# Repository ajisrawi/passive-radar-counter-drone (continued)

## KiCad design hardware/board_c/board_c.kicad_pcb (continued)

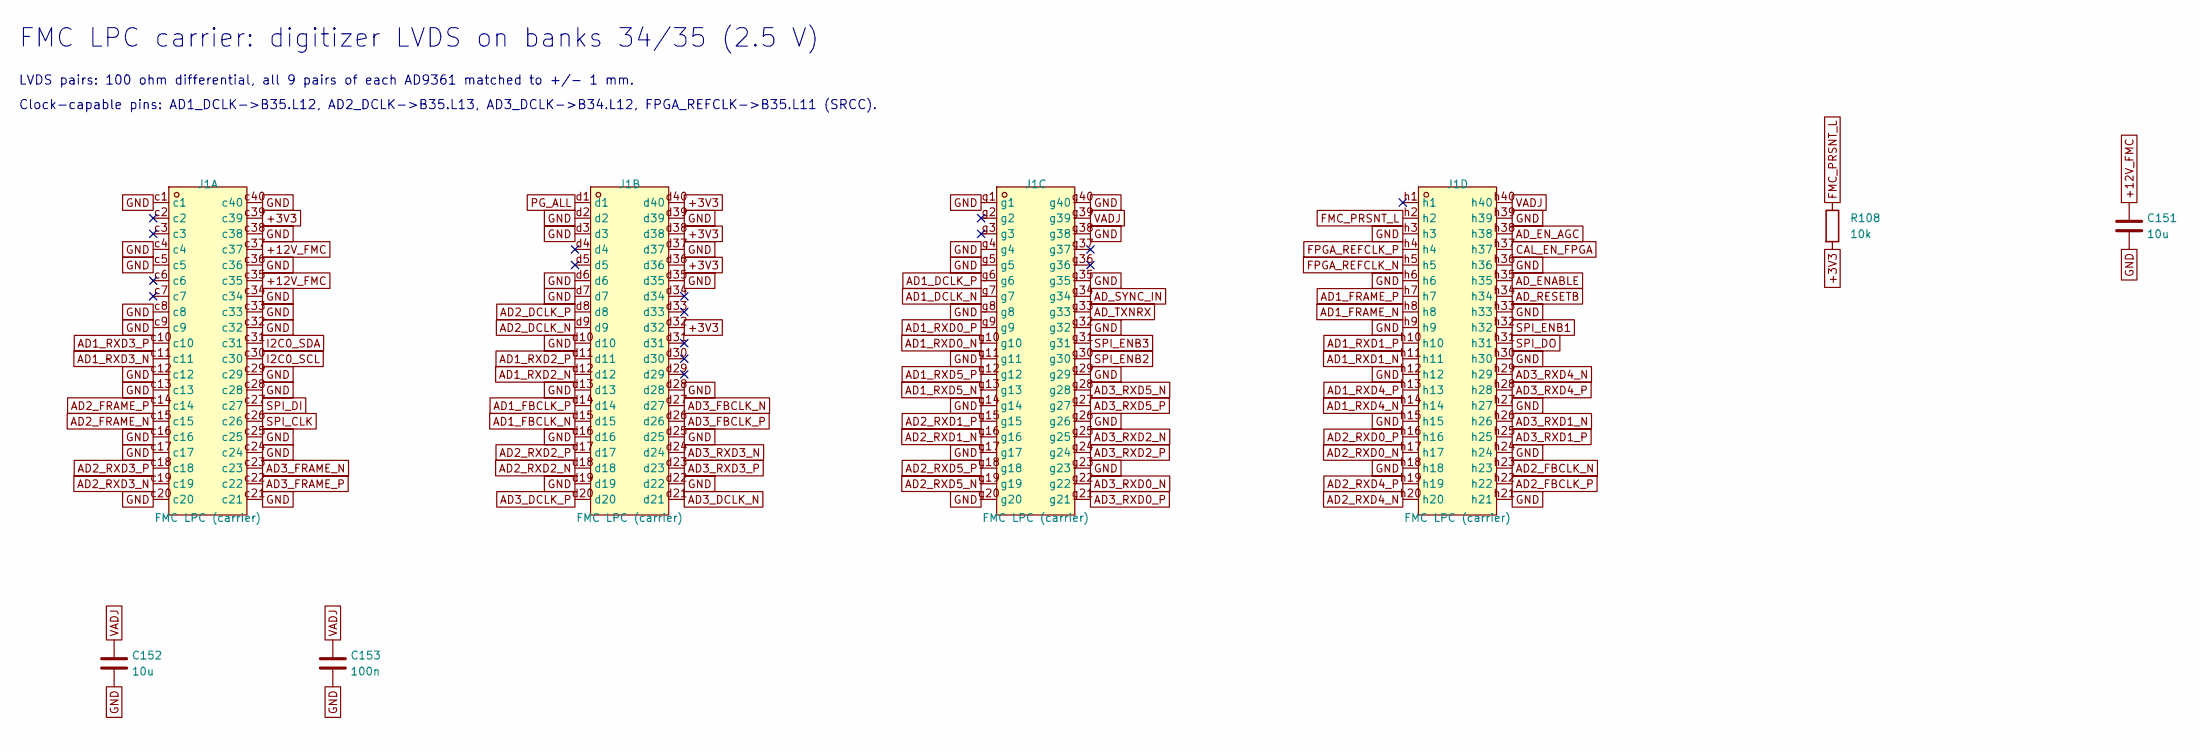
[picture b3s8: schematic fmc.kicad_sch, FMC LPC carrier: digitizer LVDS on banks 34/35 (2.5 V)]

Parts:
C151: 10u; C_0805_2012Metric
C152: 10u; C_0603_1608Metric; LCSC C19702
C153: 100n; C_0402_1005Metric; LCSC C1525
J1: FMC LPC (carrier); BGA-160_L56.6-W13.2-R4-C40-P1.27-BR; MPN ASP-134603-01; LCSC C2836665
R108: 10k; R_0402_1005Metric; LCSC C25744

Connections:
+3V3: J1.c39, J1.d32, J1.d36, J1.d38, J1.d40, R108.2; also elsewhere on the board
+12V_FMC: C151.1, J1.c35, J1.c37; also elsewhere on the board
AD1_DCLK_N: J1.g7; also elsewhere on the board
AD1_DCLK_P: J1.g6; also elsewhere on the board
AD1_FBCLK_N: J1.d15; also elsewhere on the board
AD1_FBCLK_P: J1.d14; also elsewhere on the board
AD1_FRAME_N: J1.h8; also elsewhere on the board
AD1_FRAME_P: J1.h7; also elsewhere on the board
AD1_RXD0_N: J1.g10; also elsewhere on the board
AD1_RXD0_P: J1.g9; also elsewhere on the board
AD1_RXD1_N: J1.h11; also elsewhere on the board
AD1_RXD1_P: J1.h10; also elsewhere on the board
AD1_RXD2_N: J1.d12; also elsewhere on the board
AD1_RXD2_P: J1.d11; also elsewhere on the board
AD1_RXD3_N: J1.c11; also elsewhere on the board
AD1_RXD3_P: J1.c10; also elsewhere on the board
AD1_RXD4_N: J1.h14; also elsewhere on the board
AD1_RXD4_P: J1.h13; also elsewhere on the board
AD1_RXD5_N: J1.g13; also elsewhere on the board
AD1_RXD5_P: J1.g12; also elsewhere on the board
AD2_DCLK_N: J1.d9; also elsewhere on the board
AD2_DCLK_P: J1.d8; also elsewhere on the board
AD2_FBCLK_N: J1.h23; also elsewhere on the board
AD2_FBCLK_P: J1.h22; also elsewhere on the board
AD2_FRAME_N: J1.c15; also elsewhere on the board
AD2_FRAME_P: J1.c14; also elsewhere on the board
AD2_RXD0_N: J1.h17; also elsewhere on the board
AD2_RXD0_P: J1.h16; also elsewhere on the board
AD2_RXD1_N: J1.g16; also elsewhere on the board
AD2_RXD1_P: J1.g15; also elsewhere on the board
AD2_RXD2_N: J1.d18; also elsewhere on the board
AD2_RXD2_P: J1.d17; also elsewhere on the board
AD2_RXD3_N: J1.c19; also elsewhere on the board
AD2_RXD3_P: J1.c18; also elsewhere on the board
AD2_RXD4_N: J1.h20; also elsewhere on the board
AD2_RXD4_P: J1.h19; also elsewhere on the board
AD2_RXD5_N: J1.g19; also elsewhere on the board
AD2_RXD5_P: J1.g18; also elsewhere on the board
AD3_DCLK_N: J1.d21; also elsewhere on the board
AD3_DCLK_P: J1.d20; also elsewhere on the board
AD3_FBCLK_N: J1.d27; also elsewhere on the board
AD3_FBCLK_P: J1.d26; also elsewhere on the board
AD3_FRAME_N: J1.c23; also elsewhere on the board
AD3_FRAME_P: J1.c22; also elsewhere on the board
AD3_RXD0_N: J1.g22; also elsewhere on the board
AD3_RXD0_P: J1.g21; also elsewhere on the board
AD3_RXD1_N: J1.h26; also elsewhere on the board
AD3_RXD1_P: J1.h25; also elsewhere on the board
AD3_RXD2_N: J1.g25; also elsewhere on the board
AD3_RXD2_P: J1.g24; also elsewhere on the board
AD3_RXD3_N: J1.d24; also elsewhere on the board
AD3_RXD3_P: J1.d23; also elsewhere on the board
AD3_RXD4_N: J1.h29; also elsewhere on the board
AD3_RXD4_P: J1.h28; also elsewhere on the board
AD3_RXD5_N: J1.g28; also elsewhere on the board
AD3_RXD5_P: J1.g27; also elsewhere on the board
AD_ENABLE: J1.h35; also elsewhere on the board
AD_EN_AGC: J1.h38; also elsewhere on the board
AD_RESETB: J1.h34; also elsewhere on the board
AD_SYNC_IN: J1.g34; also elsewhere on the board
AD_TXNRX: J1.g33; also elsewhere on the board
CAL_EN_FPGA: J1.h37; also elsewhere on the board
FMC_PRSNT_L: J1.h2, R108.1; also elsewhere on the board
FPGA_REFCLK_N: J1.h5; also elsewhere on the board
FPGA_REFCLK_P: J1.h4; also elsewhere on the board
GND: C151.2, C152.2, C153.2, J1.c1, J1.c4, J1.c5, J1.c8, J1.c9, J1.c12, J1.c13, J1.c16, J1.c17, J1.c20, J1.c21, J1.c24, J1.c25, J1.c28, J1.c29, J1.c32, J1.c33, J1.c34, J1.c36, J1.c38, J1.c40, J1.d2, J1.d3, J1.d6, J1.d7, J1.d10, J1.d13, J1.d16, J1.d19, J1.d22, J1.d25, J1.d28, J1.d35, J1.d37, J1.d39, J1.g1, J1.g4, J1.g5, J1.g8, J1.g11, J1.g14, J1.g17, J1.g20, J1.g23, J1.g26, J1.g29, J1.g32, J1.g35, J1.g38, J1.g40, J1.h3, J1.h6, J1.h9, J1.h12, J1.h15, J1.h18, J1.h21, J1.h24, J1.h27, J1.h30, J1.h33, J1.h36, J1.h39; also elsewhere on the board
I2C0_SCL: J1.c30; also elsewhere on the board
I2C0_SDA: J1.c31; also elsewhere on the board
PG_ALL: J1.d1; also elsewhere on the board
SPI_CLK: J1.c26; also elsewhere on the board
SPI_DI: J1.c27; also elsewhere on the board
SPI_DO: J1.h31; also elsewhere on the board
SPI_ENB1: J1.h32; also elsewhere on the board
SPI_ENB2: J1.g30; also elsewhere on the board
SPI_ENB3: J1.g31; also elsewhere on the board
VADJ: C152.1, C153.1, J1.g39, J1.h40; also elsewhere on the board

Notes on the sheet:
FMC LPC carrier: digitizer LVDS on banks 34/35 (2.5 V)
LVDS pairs: 100 ohm differential, all 9 pairs of each AD9361 matched to +/- 1 mm.
Clock-capable pins: AD1_DCLK->B35.L12, AD2_DCLK->B35.L13, AD3_DCLK->B34.L12, FPGA_REFCLK->B35.L11 (SRCC).

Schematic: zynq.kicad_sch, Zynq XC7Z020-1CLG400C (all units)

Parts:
U1: XC7Z020-1CLG400C; FBGA-400_L17.0-W17.0-R20-C20-P0.80-TL; MPN XC7Z020-1CLG400C; LCSC C2988113

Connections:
+1V0: U1.G7 (VCCPINT), U1.G11 (VCCBRAM), U1.G13 (VCCINT), U1.H10 (VCCBRAM), U1.H12 (VCCINT), U1.J7 (VCCPINT), U1.J13 (VCCINT), U1.K12 (VCCINT), U1.L7 (VCCPINT), U1.L13 (VCCINT), U1.M12 (VCCINT), U1.N7 (VCCPINT), U1.N13 (VCCINT), U1.P8 (VCCPINT), U1.P12 (VCCINT), U1.R7 (VCCPINT), U1.R13 (VCCINT); also elsewhere on the board
+1V8: U1.F8 (VCCPAUX), U1.G9 (VCCPAUX), U1.H8 (VCCPAUX), U1.J11 (VCCAUX), U1.K8 (VCCPAUX), U1.L11 (VCCAUX), U1.M8 (VCCPAUX), U1.N9 (VCCAUX), U1.N11 (VCCAUX), U1.P10 (VCCAUX), U1.R9 (VCCAUX); also elsewhere on the board
+1V35: U1.A3 (VCCO_DDR_502), U1.D2 (VCCO_DDR_502), U1.E5 (VCCO_DDR_502), U1.G1 (VCCO_DDR_502), U1.H4 (VCCO_DDR_502), U1.L3 (VCCO_DDR_502), U1.P2 (VCCO_DDR_502), U1.R5 (VCCO_DDR_502), U1.U1 (VCCO_DDR_502), U1.V4 (VCCO_DDR_502); also elsewhere on the board
+3V3: U1.A13 (VCCO_MIO1_501), U1.B6 (VCCO_MIO0_500), U1.B16 (VCCO_MIO1_501), U1.D7 (VCCO_MIO0_500), U1.D12 (VCCO_MIO1_501), U1.E15 (VCCO_MIO1_501), U1.K6 (VCCO_0), U1.M6 (CFGBVS_0), U1.N6 (RSVDVCC3), U1.R6 (RSVDVCC2), U1.T6 (RSVDVCC1), U1.T8 (VCCO_13), U1.U11 (VCCO_13), U1.W7 (VCCO_13), U1.Y10 (VCCO_13); also elsewhere on the board
AD1_DCLK_N: U1.K18 (IO_L12N_T1_MRCC_35); also elsewhere on the board
AD1_DCLK_P: U1.K17 (IO_L12P_T1_MRCC_35); also elsewhere on the board
AD1_FBCLK_N: U1.M18 (IO_L8N_T1_AD10N_35); also elsewhere on the board
AD1_FBCLK_P: U1.M17 (IO_L8P_T1_AD10P_35); also elsewhere on the board
AD1_FRAME_N: U1.B20 (IO_L1N_T0_AD0N_35); also elsewhere on the board
AD1_FRAME_P: U1.C20 (IO_L1P_T0_AD0P_35); also elsewhere on the board
AD1_RXD0_N: U1.A20 (IO_L2N_T0_AD8N_35); also elsewhere on the board
AD1_RXD0_P: U1.B19 (IO_L2P_T0_AD8P_35); also elsewhere on the board
AD1_RXD1_N: U1.D18 (IO_L3N_T0_DQS_AD1N_35); also elsewhere on the board
AD1_RXD1_P: U1.E17 (IO_L3P_T0_DQS_AD1P_35); also elsewhere on the board
AD1_RXD2_N: U1.D20 (IO_L4N_T0_35); also elsewhere on the board
AD1_RXD2_P: U1.D19 (IO_L4P_T0_35); also elsewhere on the board
AD1_RXD3_N: U1.E19 (IO_L5N_T0_AD9N_35); also elsewhere on the board
AD1_RXD3_P: U1.E18 (IO_L5P_T0_AD9P_35); also elsewhere on the board
AD1_RXD4_N: U1.F17 (IO_L6N_T0_VREF_35); also elsewhere on the board
AD1_RXD4_P: U1.F16 (IO_L6P_T0_35); also elsewhere on the board
AD1_RXD5_N: U1.M20 (IO_L7N_T1_AD2N_35); also elsewhere on the board
AD1_RXD5_P: U1.M19 (IO_L7P_T1_AD2P_35); also elsewhere on the board
AD2_DCLK_N: U1.H17 (IO_L13N_T2_MRCC_35); also elsewhere on the board
AD2_DCLK_P: U1.H16 (IO_L13P_T2_MRCC_35); also elsewhere on the board
AD2_FBCLK_N: U1.G15 (IO_L19N_T3_VREF_35); also elsewhere on the board
AD2_FBCLK_P: U1.H15 (IO_L19P_T3_35); also elsewhere on the board
AD2_FRAME_N: U1.L20 (IO_L9N_T1_DQS_AD3N_35); also elsewhere on the board
AD2_FRAME_P: U1.L19 (IO_L9P_T1_DQS_AD3P_35); also elsewhere on the board
AD2_RXD0_N: U1.J19 (IO_L10N_T1_AD11N_35); also elsewhere on the board
AD2_RXD0_P: U1.K19 (IO_L10P_T1_AD11P_35); also elsewhere on the board
AD2_RXD1_N: U1.H18 (IO_L14N_T2_AD4N_SRCC_35); also elsewhere on the board
AD2_RXD1_P: U1.J18 (IO_L14P_T2_AD4P_SRCC_35); also elsewhere on the board
AD2_RXD2_N: U1.F20 (IO_L15N_T2_DQS_AD12N_35); also elsewhere on the board
AD2_RXD2_P: U1.F19 (IO_L15P_T2_DQS_AD12P_35); also elsewhere on the board
AD2_RXD3_N: U1.G18 (IO_L16N_T2_35); also elsewhere on the board
AD2_RXD3_P: U1.G17 (IO_L16P_T2_35); also elsewhere on the board
AD2_RXD4_N: U1.H20 (IO_L17N_T2_AD5N_35); also elsewhere on the board
AD2_RXD4_P: U1.J20 (IO_L17P_T2_AD5P_35); also elsewhere on the board
AD2_RXD5_N: U1.G20 (IO_L18N_T2_AD13N_35); also elsewhere on the board
AD2_RXD5_P: U1.G19 (IO_L18P_T2_AD13P_35); also elsewhere on the board
AD3_DCLK_N: U1.U19 (IO_L12N_T1_MRCC_34); also elsewhere on the board
AD3_DCLK_P: U1.U18 (IO_L12P_T1_MRCC_34); also elsewhere on the board
AD3_FBCLK_N: U1.U17 (IO_L9N_T1_DQS_34); also elsewhere on the board
AD3_FBCLK_P: U1.T16 (IO_L9P_T1_DQS_34); also elsewhere on the board
AD3_FRAME_N: U1.T10 (IO_L1N_T0_34); also elsewhere on the board
AD3_FRAME_P: U1.T11 (IO_L1P_T0_34); also elsewhere on the board
AD3_RXD0_N: U1.U12 (IO_L2N_T0_34); also elsewhere on the board
AD3_RXD0_P: U1.T12 (IO_L2P_T0_34); also elsewhere on the board
AD3_RXD1_N: U1.W13 (IO_L4N_T0_34); also elsewhere on the board
AD3_RXD1_P: U1.V12 (IO_L4P_T0_34); also elsewhere on the board
AD3_RXD2_N: U1.T15 (IO_L5N_T0_34); also elsewhere on the board
AD3_RXD2_P: U1.T14 (IO_L5P_T0_34); also elsewhere on the board
AD3_RXD3_N: U1.R14 (IO_L6N_T0_VREF_34); also elsewhere on the board
AD3_RXD3_P: U1.P14 (IO_L6P_T0_34); also elsewhere on the board
AD3_RXD4_N: U1.Y17 (IO_L7N_T1_34); also elsewhere on the board
AD3_RXD4_P: U1.Y16 (IO_L7P_T1_34); also elsewhere on the board
AD3_RXD5_N: U1.Y14 (IO_L8N_T1_34); also elsewhere on the board
AD3_RXD5_P: U1.W14 (IO_L8P_T1_34); also elsewhere on the board
AD_ENABLE: U1.P20 (IO_L14N_T2_SRCC_34); also elsewhere on the board
AD_EN_AGC: U1.W20 (IO_L16N_T2_34); also elsewhere on the board
AD_RESETB: U1.N20 (IO_L14P_T2_SRCC_34); also elsewhere on the board
AD_SYNC_IN: U1.U20 (IO_L15N_T2_DQS_34); also elsewhere on the board
AD_TXNRX: U1.T20 (IO_L15P_T2_DQS_34); also elsewhere on the board
CAL_EN_FPGA: U1.V20 (IO_L16P_T2_34); also elsewhere on the board
DDR_A0: U1.N2 (PS_DDR_A0_502); also elsewhere on the board
DDR_A1: U1.K2 (PS_DDR_A1_502); also elsewhere on the board
DDR_A2: U1.M3 (PS_DDR_A2_502); also elsewhere on the board
DDR_A3: U1.K3 (PS_DDR_A3_502); also elsewhere on the board
DDR_A4: U1.M4 (PS_DDR_A4_502); also elsewhere on the board
DDR_A5: U1.L1 (PS_DDR_A5_502); also elsewhere on the board
DDR_A6: U1.L4 (PS_DDR_A6_502); also elsewhere on the board
DDR_A7: U1.K4 (PS_DDR_A7_502); also elsewhere on the board
DDR_A8: U1.K1 (PS_DDR_A8_502); also elsewhere on the board
DDR_A9: U1.J4 (PS_DDR_A9_502); also elsewhere on the board
DDR_A10: U1.F5 (PS_DDR_A10_502); also elsewhere on the board
DDR_A11: U1.G4 (PS_DDR_A11_502); also elsewhere on the board
DDR_A12: U1.E4 (PS_DDR_A12_502); also elsewhere on the board
DDR_A13: U1.D4 (PS_DDR_A13_502); also elsewhere on the board
DDR_A14: U1.F4 (PS_DDR_A14_502); also elsewhere on the board
DDR_BA0: U1.L5 (PS_DDR_BA0_502); also elsewhere on the board
DDR_BA1: U1.R4 (PS_DDR_BA1_502); also elsewhere on the board
DDR_BA2: U1.J5 (PS_DDR_BA2_502); also elsewhere on the board
DDR_CAS_B: U1.P5 (PS_DDR_CAS_B_502); also elsewhere on the board
DDR_CKE: U1.N3 (PS_DDR_CKE_502); also elsewhere on the board
DDR_CK_N: U1.M2 (PS_DDR_CKN_502); also elsewhere on the board
DDR_CK_P: U1.L2 (PS_DDR_CKP_502); also elsewhere on the board
DDR_CS_B: U1.N1 (PS_DDR_CS_B_502); also elsewhere on the board
DDR_DM0: U1.A1 (PS_DDR_DM0_502); also elsewhere on the board
DDR_DM1: U1.F1 (PS_DDR_DM1_502); also elsewhere on the board
DDR_DQ0: U1.C3 (PS_DDR_DQ0_502); also elsewhere on the board
DDR_DQ1: U1.B3 (PS_DDR_DQ1_502); also elsewhere on the board
DDR_DQ2: U1.A2 (PS_DDR_DQ2_502); also elsewhere on the board
DDR_DQ3: U1.A4 (PS_DDR_DQ3_502); also elsewhere on the board
DDR_DQ4: U1.D3 (PS_DDR_DQ4_502); also elsewhere on the board
DDR_DQ5: U1.D1 (PS_DDR_DQ5_502); also elsewhere on the board
DDR_DQ6: U1.C1 (PS_DDR_DQ6_502); also elsewhere on the board
DDR_DQ7: U1.E1 (PS_DDR_DQ7_502); also elsewhere on the board
DDR_DQ8: U1.E2 (PS_DDR_DQ8_502); also elsewhere on the board
DDR_DQ9: U1.E3 (PS_DDR_DQ9_502); also elsewhere on the board
DDR_DQ10: U1.G3 (PS_DDR_DQ10_502); also elsewhere on the board
DDR_DQ11: U1.H3 (PS_DDR_DQ11_502); also elsewhere on the board
DDR_DQ12: U1.J3 (PS_DDR_DQ12_502); also elsewhere on the board
DDR_DQ13: U1.H2 (PS_DDR_DQ13_502); also elsewhere on the board
DDR_DQ14: U1.H1 (PS_DDR_DQ14_502); also elsewhere on the board
DDR_DQ15: U1.J1 (PS_DDR_DQ15_502); also elsewhere on the board
DDR_DQS0_N: U1.B2 (PS_DDR_DQS_N0_502); also elsewhere on the board
DDR_DQS0_P: U1.C2 (PS_DDR_DQS_P0_502); also elsewhere on the board
DDR_DQS1_N: U1.F2 (PS_DDR_DQS_N1_502); also elsewhere on the board
DDR_DQS1_P: U1.G2 (PS_DDR_DQS_P1_502); also elsewhere on the board
DDR_ODT: U1.N5 (PS_DDR_ODT_502); also elsewhere on the board
DDR_RAS_B: U1.P4 (PS_DDR_RAS_B_502); also elsewhere on the board
DDR_RESET_B: U1.B4 (PS_DDR_DRST_B_502); also elsewhere on the board
DDR_VREF: U1.H6 (PS_DDR_VREF0_502), U1.P6 (PS_DDR_VREF1_502); also elsewhere on the board
DDR_VRN: U1.G5 (PS_DDR_VRN_502); also elsewhere on the board
DDR_VRP: U1.H5 (PS_DDR_VRP_502); also elsewhere on the board
DDR_WE_B: U1.M5 (PS_DDR_WE_B_502); also elsewhere on the board
DONE: U1.R11 (DONE_0); also elsewhere on the board
ETH_MDC: U1.C10 (PS_MIO52_501); also elsewhere on the board
ETH_MDIO: U1.C11 (PS_MIO53_501); also elsewhere on the board
ETH_RSTN: U1.B14 (PS_MIO47_501); also elsewhere on the board
FMC_PRSNT_L: U1.Y9 (IO_L14P_T2_SRCC_13); also elsewhere on the board
FPGA_REFCLK_N: U1.L17 (IO_L11N_T1_SRCC_35); also elsewhere on the board
FPGA_REFCLK_P: U1.L16 (IO_L11P_T1_SRCC_35); also elsewhere on the board
GND: U1.A8 (GND), U1.A18 (GND), U1.B1 (GND), U1.B11 (GND), U1.C4 (GND), U1.C9 (GND), U1.C14 (GND), U1.D17 (GND), U1.E10 (GND), U1.E20 (GND), U1.F3 (GND), U1.F7 (GND), U1.F10 (RSVDGND), U1.F11 (VCCBATT_0), U1.G10 (GND), U1.G12 (GND), U1.G16 (GND), U1.H7 (GND), U1.H9 (GND), U1.H11 (GND), U1.H13 (GND), U1.H19 (GND), U1.J2 (GND), U1.J8 (GND), U1.J12 (GND), U1.K5 (GND), U1.K7 (GND), U1.K11 (GND), U1.K13 (GND), U1.K15 (GND), U1.L8 (GND), U1.L12 (GND), U1.L18 (GND), U1.M1 (GND), U1.M7 (GND), U1.M11 (GND), U1.M13 (GND), U1.N4 (GND), U1.N8 (GND), U1.N10 (GND), U1.N12 (GND), U1.N14 (GND), U1.P7 (GND), U1.P9 (GND), U1.P11 (GND), U1.P13 (GND), U1.P17 (GND), U1.R8 (GND), U1.R12 (GND), U1.R20 (GND), U1.T3 (GND), U1.T7 (GND), U1.T13 (GND), U1.U6 (GND), U1.U16 (GND), U1.V9 (GND), U1.V19 (GND), U1.W2 (GND), U1.W12 (GND), U1.Y5 (GND), U1.Y15 (GND); also elsewhere on the board
GNDADC: U1.J10 (GNDADC_0), U1.K9 (VP_0), U1.K10 (VREFN_0), U1.L9 (VREFP_0), U1.L10 (VN_0); also elsewhere on the board
GNSS_PPS: U1.U7 (IO_L11P_T1_SRCC_13); also elsewhere on the board
GNSS_RESETN: U1.U10 (IO_L12N_T1_MRCC_13); also elsewhere on the board
GNSS_RXD: U1.T9 (IO_L12P_T1_MRCC_13); also elsewhere on the board
GNSS_TXD: U1.V7 (IO_L11N_T1_SRCC_13); also elsewhere on the board
I2C0_SCL: U1.E9 (PS_MIO10_500); also elsewhere on the board
I2C0_SDA: U1.C6 (PS_MIO11_500); also elsewhere on the board
INIT_B: U1.R10 (INIT_B_0); also elsewhere on the board
JTAG_TCK: U1.F9 (TCK_0); also elsewhere on the board
JTAG_TDI: U1.G6 (TDI_0); also elsewhere on the board
JTAG_TDO: U1.F6 (TDO_0); also elsewhere on the board
JTAG_TMS: U1.J6 (TMS_0); also elsewhere on the board
LED_PL0: U1.Y7 (IO_L13P_T2_MRCC_13); also elsewhere on the board
LED_PL1: U1.Y6 (IO_L13N_T2_MRCC_13); also elsewhere on the board
LED_PS: U1.E6 (PS_MIO0_500); also elsewhere on the board
MIO_VREF: U1.E11 (PS_MIO_VREF_501); also elsewhere on the board
PROGRAM_B: U1.L6 (PROGRAM_B_0); also elsewhere on the board
PS_CLK: U1.E7 (PS_CLK_500); also elsewhere on the board
PS_POR_B: U1.C7 (PS_POR_B_500); also elsewhere on the board
PS_SRST_B: U1.B10 (PS_SRST_B_501); also elsewhere on the board
PUDC_B: U1.U13 (IO_L3P_T0_DQS_PUDC_B_34); also elsewhere on the board
QSPI_CLK: U1.A5 (PS_MIO6_500); also elsewhere on the board
QSPI_CS: U1.A7 (PS_MIO1_500); also elsewhere on the board
QSPI_IO0: U1.B8 (PS_MIO2_500); also elsewhere on the board
QSPI_IO1: U1.D6 (PS_MIO3_500); also elsewhere on the board
QSPI_IO2: U1.B7 (PS_MIO4_500); also elsewhere on the board
QSPI_IO3: U1.A6 (PS_MIO5_500); also elsewhere on the board
RGMII_RXC: U1.B17 (PS_MIO22_501); also elsewhere on the board
RGMII_RXCTL: U1.D13 (PS_MIO27_501); also elsewhere on the board
RGMII_RXD0: U1.D11 (PS_MIO23_501); also elsewhere on the board
RGMII_RXD1: U1.A16 (PS_MIO24_501); also elsewhere on the board
RGMII_RXD2: U1.F15 (PS_MIO25_501); also elsewhere on the board
RGMII_RXD3: U1.A15 (PS_MIO26_501); also elsewhere on the board
RGMII_TXC: U1.A19 (PS_MIO16_501); also elsewhere on the board
RGMII_TXCTL: U1.F14 (PS_MIO21_501); also elsewhere on the board
RGMII_TXD0: U1.E14 (PS_MIO17_501); also elsewhere on the board
RGMII_TXD1: U1.B18 (PS_MIO18_501); also elsewhere on the board
RGMII_TXD2: U1.D10 (PS_MIO19_501); also elsewhere on the board
RGMII_TXD3: U1.A17 (PS_MIO20_501); also elsewhere on the board
SD_CD: U1.D16 (PS_MIO46_501); also elsewhere on the board
SD_CLK_MIO: U1.D14 (PS_MIO40_501); also elsewhere on the board
SD_CMD: U1.C17 (PS_MIO41_501); also elsewhere on the board
SD_D0: U1.E12 (PS_MIO42_501); also elsewhere on the board
SD_D1: U1.A9 (PS_MIO43_501); also elsewhere on the board
SD_D2: U1.F13 (PS_MIO44_501); also elsewhere on the board
SD_D3: U1.B15 (PS_MIO45_501); also elsewhere on the board
SPI_CLK: U1.V15 (IO_L10P_T1_34); also elsewhere on the board
SPI_DI: U1.W15 (IO_L10N_T1_34); also elsewhere on the board
SPI_DO: U1.U14 (IO_L11P_T1_SRCC_34); also elsewhere on the board
SPI_ENB1: U1.U15 (IO_L11N_T1_SRCC_34); also elsewhere on the board
SPI_ENB2: U1.N18 (IO_L13P_T2_MRCC_34); also elsewhere on the board
SPI_ENB3: U1.P19 (IO_L13N_T2_MRCC_34); also elsewhere on the board
STRAP_MIO7: U1.D8 (PS_MIO7_500); also elsewhere on the board
STRAP_MIO8: U1.D5 (PS_MIO8_500); also elsewhere on the board
UART_RX: U1.C12 (PS_MIO49_501); also elsewhere on the board
UART_TX: U1.B12 (PS_MIO48_501); also elsewhere on the board
USER_BTN_PS: U1.B5 (PS_MIO9_500); also elsewhere on the board
VADJ: U1.C19 (VCCO_35), U1.F18 (VCCO_35), U1.H14 (VCCO_35), U1.J17 (VCCO_35), U1.K20 (VCCO_35), U1.M16 (VCCO_35), U1.N19 (VCCO_34), U1.R15 (VCCO_34), U1.T18 (VCCO_34), U1.V14 (VCCO_34), U1.W17 (VCCO_34), U1.Y20 (VCCO_34); also elsewhere on the board
VCCADC: U1.J9 (VCCADC_0); also elsewhere on the board
VCCPLL: U1.G8 (VCCPLL); also elsewhere on the board

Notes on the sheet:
Zynq XC7Z020-1CLG400C (all units)

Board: 8 copper layers, 314 parts (55 on the bottom side), 251 nets, no tracks yet.

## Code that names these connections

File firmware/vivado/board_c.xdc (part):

# board_c: PL pins generated from board_c/board_c.netlist.json by firmware/vivado/gen_xdc.py - do not edit
# FPGA U1 = prc:XC7Z020-1CLG400C

set_property PACKAGE_PIN K18 [get_ports {ad1_dclk_n}]   ;# IO_L12N_T1_MRCC_35
set_property IOSTANDARD LVDS_25 [get_ports {ad1_dclk_n}]
set_property DIFF_TERM TRUE [get_ports {ad1_dclk_n}]
set_property PACKAGE_PIN K17 [get_ports {ad1_dclk_p}]   ;# IO_L12P_T1_MRCC_35
set_property IOSTANDARD LVDS_25 [get_ports {ad1_dclk_p}]
set_property DIFF_TERM TRUE [get_ports {ad1_dclk_p}]
set_property PACKAGE_PIN M18 [get_ports {ad1_fbclk_n}]   ;# IO_L8N_T1_AD10N_35
set_property IOSTANDARD LVDS_25 [get_ports {ad1_fbclk_n}]
set_property PACKAGE_PIN M17 [get_ports {ad1_fbclk_p}]   ;# IO_L8P_T1_AD10P_35
set_property IOSTANDARD LVDS_25 [get_ports {ad1_fbclk_p}]
set_property PACKAGE_PIN B20 [get_ports {ad1_frame_n}]   ;# IO_L1N_T0_AD0N_35
set_property IOSTANDARD LVDS_25 [get_ports {ad1_frame_n}]
set_property DIFF_TERM TRUE [get_ports {ad1_frame_n}]
set_property PACKAGE_PIN C20 [get_ports {ad1_frame_p}]   ;# IO_L1P_T0_AD0P_35
set_property IOSTANDARD LVDS_25 [get_ports {ad1_frame_p}]
set_property DIFF_TERM TRUE [get_ports {ad1_frame_p}]
set_property PACKAGE_PIN A20 [get_ports {ad1_rxd0_n}]   ;# IO_L2N_T0_AD8N_35
set_property IOSTANDARD LVDS_25 [get_ports {ad1_rxd0_n}]
set_property DIFF_TERM TRUE [get_ports {ad1_rxd0_n}]
set_property PACKAGE_PIN B19 [get_ports {ad1_rxd0_p}]   ;# IO_L2P_T0_AD8P_35
set_property IOSTANDARD LVDS_25 [get_ports {ad1_rxd0_p}]
set_property DIFF_TERM TRUE [get_ports {ad1_rxd0_p}]
set_property PACKAGE_PIN D18 [get_ports {ad1_rxd1_n}]   ;# IO_L3N_T0_DQS_AD1N_35
set_property IOSTANDARD LVDS_25 [get_ports {ad1_rxd1_n}]
set_property DIFF_TERM TRUE [get_ports {ad1_rxd1_n}]
set_property PACKAGE_PIN E17 [get_ports {ad1_rxd1_p}]   ;# IO_L3P_T0_DQS_AD1P_35
set_property IOSTANDARD LVDS_25 [get_ports {ad1_rxd1_p}]
set_property DIFF_TERM TRUE [get_ports {ad1_rxd1_p}]
set_property PACKAGE_PIN D20 [get_ports {ad1_rxd2_n}]   ;# IO_L4N_T0_35
set_property IOSTANDARD LVDS_25 [get_ports {ad1_rxd2_n}]
set_property DIFF_TERM TRUE [get_ports {ad1_rxd2_n}]
set_property PACKAGE_PIN D19 [get_ports {ad1_rxd2_p}]   ;# IO_L4P_T0_35
set_property IOSTANDARD LVDS_25 [get_ports {ad1_rxd2_p}]
set_property DIFF_TERM TRUE [get_ports {ad1_rxd2_p}]
set_property PACKAGE_PIN E19 [get_ports {ad1_rxd3_n}]   ;# IO_L5N_T0_AD9N_35
set_property IOSTANDARD LVDS_25 [get_ports {ad1_rxd3_n}]
set_property DIFF_TERM TRUE [get_ports {ad1_rxd3_n}]
set_property PACKAGE_PIN E18 [get_ports {ad1_rxd3_p}]   ;# IO_L5P_T0_AD9P_35
set_property IOSTANDARD LVDS_25 [get_ports {ad1_rxd3_p}]
set_property DIFF_TERM TRUE [get_ports {ad1_rxd3_p}]
set_property PACKAGE_PIN F17 [get_ports {ad1_rxd4_n}]   ;# IO_L6N_T0_VREF_35
set_property IOSTANDARD LVDS_25 [get_ports {ad1_rxd4_n}]
set_property DIFF_TERM TRUE [get_ports {ad1_rxd4_n}]
set_property PACKAGE_PIN F16 [get_ports {ad1_rxd4_p}]   ;# IO_L6P_T0_35
set_property IOSTANDARD LVDS_25 [get_ports {ad1_rxd4_p}]
set_property DIFF_TERM TRUE [get_ports {ad1_rxd4_p}]
set_property PACKAGE_PIN M20 [get_ports {ad1_rxd5_n}]   ;# IO_L7N_T1_AD2N_35
set_property IOSTANDARD LVDS_25 [get_ports {ad1_rxd5_n}]
set_property DIFF_TERM TRUE [get_ports {ad1_rxd5_n}]
set_property PACKAGE_PIN M19 [get_ports {ad1_rxd5_p}]   ;# IO_L7P_T1_AD2P_35
set_property IOSTANDARD LVDS_25 [get_ports {ad1_rxd5_p}]
set_property DIFF_TERM TRUE [get_ports {ad1_rxd5_p}]
set_property PACKAGE_PIN H17 [get_ports {ad2_dclk_n}]   ;# IO_L13N_T2_MRCC_35
set_property IOSTANDARD LVDS_25 [get_ports {ad2_dclk_n}]
set_property DIFF_TERM TRUE [get_ports {ad2_dclk_n}]
set_property PACKAGE_PIN H16 [get_ports {ad2_dclk_p}]   ;# IO_L13P_T2_MRCC_35
set_property IOSTANDARD LVDS_25 [get_ports {ad2_dclk_p}]
set_property DIFF_TERM TRUE [get_ports {ad2_dclk_p}]
set_property PACKAGE_PIN G15 [get_ports {ad2_fbclk_n}]   ;# IO_L19N_T3_VREF_35
set_property IOSTANDARD LVDS_25 [get_ports {ad2_fbclk_n}]
set_property PACKAGE_PIN H15 [get_ports {ad2_fbclk_p}]   ;# IO_L19P_T3_35
set_property IOSTANDARD LVDS_25 [get_ports {ad2_fbclk_p}]
set_property PACKAGE_PIN L20 [get_ports {ad2_frame_n}]   ;# IO_L9N_T1_DQS_AD3N_35
set_property IOSTANDARD LVDS_25 [get_ports {ad2_frame_n}]
set_property DIFF_TERM TRUE [get_ports {ad2_frame_n}]
set_property PACKAGE_PIN L19 [get_ports {ad2_frame_p}]   ;# IO_L9P_T1_DQS_AD3P_35
set_property IOSTANDARD LVDS_25 [get_ports {ad2_frame_p}]
set_property DIFF_TERM TRUE [get_ports {ad2_frame_p}]
set_property PACKAGE_PIN J19 [get_ports {ad2_rxd0_n}]   ;# IO_L10N_T1_AD11N_35
set_property IOSTANDARD LVDS_25 [get_ports {ad2_rxd0_n}]
set_property DIFF_TERM TRUE [get_ports {ad2_rxd0_n}]
set_property PACKAGE_PIN K19 [get_ports {ad2_rxd0_p}]   ;# IO_L10P_T1_AD11P_35
set_property IOSTANDARD LVDS_25 [get_ports {ad2_rxd0_p}]
set_property DIFF_TERM TRUE [get_ports {ad2_rxd0_p}]
set_property PACKAGE_PIN H18 [get_ports {ad2_rxd1_n}]   ;# IO_L14N_T2_AD4N_SRCC_35
set_property IOSTANDARD LVDS_25 [get_ports {ad2_rxd1_n}]
set_property DIFF_TERM TRUE [get_ports {ad2_rxd1_n}]
set_property PACKAGE_PIN J18 [get_ports {ad2_rxd1_p}]   ;# IO_L14P_T2_AD4P_SRCC_35
set_property IOSTANDARD LVDS_25 [get_ports {ad2_rxd1_p}]
set_property DIFF_TERM TRUE [get_ports {ad2_rxd1_p}]
set_property PACKAGE_PIN F20 [get_ports {ad2_rxd2_n}]   ;# IO_L15N_T2_DQS_AD12N_35
set_property IOSTANDARD LVDS_25 [get_ports {ad2_rxd2_n}]
set_property DIFF_TERM TRUE [get_ports {ad2_rxd2_n}]
set_property PACKAGE_PIN F19 [get_ports {ad2_rxd2_p}]   ;# IO_L15P_T2_DQS_AD12P_35
set_property IOSTANDARD LVDS_25 [get_ports {ad2_rxd2_p}]
set_property DIFF_TERM TRUE [get_ports {ad2_rxd2_p}]
set_property PACKAGE_PIN G18 [get_ports {ad2_rxd3_n}]   ;# IO_L16N_T2_35
set_property IOSTANDARD LVDS_25 [get_ports {ad2_rxd3_n}]
set_property DIFF_TERM TRUE [get_ports {ad2_rxd3_n}]
set_property PACKAGE_PIN G17 [get_ports {ad2_rxd3_p}]   ;# IO_L16P_T2_35
set_property IOSTANDARD LVDS_25 [get_ports {ad2_rxd3_p}]
set_property DIFF_TERM TRUE [get_ports {ad2_rxd3_p}]
set_property PACKAGE_PIN H20 [get_ports {ad2_rxd4_n}]   ;# IO_L17N_T2_AD5N_35
set_property IOSTANDARD LVDS_25 [get_ports {ad2_rxd4_n}]
set_property DIFF_TERM TRUE [get_ports {ad2_rxd4_n}]
set_property PACKAGE_PIN J20 [get_ports {ad2_rxd4_p}]   ;# IO_L17P_T2_AD5P_35
set_property IOSTANDARD LVDS_25 [get_ports {ad2_rxd4_p}]
set_property DIFF_TERM TRUE [get_ports {ad2_rxd4_p}]
set_property PACKAGE_PIN G20 [get_ports {ad2_rxd5_n}]   ;# IO_L18N_T2_AD13N_35
set_property IOSTANDARD LVDS_25 [get_ports {ad2_rxd5_n}]
set_property DIFF_TERM TRUE [get_ports {ad2_rxd5_n}]
set_property PACKAGE_PIN G19 [get_ports {ad2_rxd5_p}]   ;# IO_L18P_T2_AD13P_35
set_property IOSTANDARD LVDS_25 [get_ports {ad2_rxd5_p}]
set_property DIFF_TERM TRUE [get_ports {ad2_rxd5_p}]
set_property PACKAGE_PIN U19 [get_ports {ad3_dclk_n}]   ;# IO_L12N_T1_MRCC_34
set_property IOSTANDARD LVDS_25 [get_ports {ad3_dclk_n}]
set_property DIFF_TERM TRUE [get_ports {ad3_dclk_n}]
set_property PACKAGE_PIN U18 [get_ports {ad3_dclk_p}]   ;# IO_L12P_T1_MRCC_34
set_property IOSTANDARD LVDS_25 [get_ports {ad3_dclk_p}]
set_property DIFF_TERM TRUE [get_ports {ad3_dclk_p}]
set_property PACKAGE_PIN U17 [get_ports {ad3_fbclk_n}]   ;# IO_L9N_T1_DQS_34
set_property IOSTANDARD LVDS_25 [get_ports {ad3_fbclk_n}]
set_property PACKAGE_PIN T16 [get_ports {ad3_fbclk_p}]   ;# IO_L9P_T1_DQS_34
set_property IOSTANDARD LVDS_25 [get_ports {ad3_fbclk_p}]
set_property PACKAGE_PIN T10 [get_ports {ad3_frame_n}]   ;# IO_L1N_T0_34
set_property IOSTANDARD LVDS_25 [get_ports {ad3_frame_n}]
set_property DIFF_TERM TRUE [get_ports {ad3_frame_n}]
set_property PACKAGE_PIN T11 [get_ports {ad3_frame_p}]   ;# IO_L1P_T0_34
set_property IOSTANDARD LVDS_25 [get_ports {ad3_frame_p}]
set_property DIFF_TERM TRUE [get_ports {ad3_frame_p}]
set_property PACKAGE_PIN U12 [get_ports {ad3_rxd0_n}]   ;# IO_L2N_T0_34
set_property IOSTANDARD LVDS_25 [get_ports {ad3_rxd0_n}]
set_property DIFF_TERM TRUE [get_ports {ad3_rxd0_n}]
set_property PACKAGE_PIN T12 [get_ports {ad3_rxd0_p}]   ;# IO_L2P_T0_34
set_property IOSTANDARD LVDS_25 [get_ports {ad3_rxd0_p}]
set_property DIFF_TERM TRUE [get_ports {ad3_rxd0_p}]
set_property PACKAGE_PIN W13 [get_ports {ad3_rxd1_n}]   ;# IO_L4N_T0_34
set_property IOSTANDARD LVDS_25 [get_ports {ad3_rxd1_n}]
set_property DIFF_TERM TRUE [get_ports {ad3_rxd1_n}]
set_property PACKAGE_PIN V12 [get_ports {ad3_rxd1_p}]   ;# IO_L4P_T0_34
set_property IOSTANDARD LVDS_25 [get_ports {ad3_rxd1_p}]
set_property DIFF_TERM TRUE [get_ports {ad3_rxd1_p}]
set_property PACKAGE_PIN T15 [get_ports {ad3_rxd2_n}]   ;# IO_L5N_T0_34
set_property IOSTANDARD LVDS_25 [get_ports {ad3_rxd2_n}]
set_property DIFF_TERM TRUE [get_ports {ad3_rxd2_n}]
set_property PACKAGE_PIN T14 [get_ports {ad3_rxd2_p}]   ;# IO_L5P_T0_34
set_property IOSTANDARD LVDS_25 [get_ports {ad3_rxd2_p}]
set_property DIFF_TERM TRUE [get_ports {ad3_rxd2_p}]
set_property PACKAGE_PIN R14 [get_ports {ad3_rxd3_n}]   ;# IO_L6N_T0_VREF_34
set_property IOSTANDARD LVDS_25 [get_ports {ad3_rxd3_n}]
set_property DIFF_TERM TRUE [get_ports {ad3_rxd3_n}]
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
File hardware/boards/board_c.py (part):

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        pw.add(Part(ref("H"), "Mechanical:MountingHole_Pad", "M3", FP["HOLE"], {"1": "GND"}))
    for net in ("+1V0", "+1V8", "+1V35", "+3V3", "VADJ", "DDR_VTT"):
        pw.add(Part(ref("TP"), "Connector:TestPoint", net, FP["TP"], {"1": net}))
    pw.note("Sequence: 1.0 V (VCCINT/VCCPINT) -> 1.8 V (VCCAUX/VCCPAUX) -> 1.35 V, 3.3 V, 2.5 V -> PS_POR_B.")

    # ================================================================ Zynq power + config
    zp = d.sheet("zynq_power", "Zynq power pins, configuration, JTAG, XADC")
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    ps.add(R(ref("R"), "20k", "QSPI_IO3", "+3V3"))
    ps.add(R(ref("R"), "4.7k", "+3V3", "BOOT_SD_J"))
    ps.add(Part(ref("J"), "Connector_Generic:Conn_01x02", "BOOT: open=QSPI, closed=SD",
                "Connector_PinHeader_2.54mm:PinHeader_1x02_P2.54mm_Vertical", {"1": "BOOT_SD_J", "2": "QSPI_IO2"}))
    # QSPI boot flash
    ps.add(Part(ref("U"), "prc:W25Q256JVEIQTR", "W25Q256JVEIQ", None,
                {"~{CS}": "QSPI_CS", "DO(IO1)": "QSPI_IO1", "WP#(IO2)": "QSPI_IO2", "DI(IO0)": "QSPI_IO0",
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        et.add(R(ref("R"), "22", a, b))
    straps = {"PHY_RXD0": "+3V3",   # RXDLY = 1: PHY adds 2 ns RX clock delay
              "PHY_RXD1": "+3V3",   # TXDLY = 1: PHY adds 2 ns TX clock delay
              "PHY_RXD2": "GND",    # PLLOFF = 0
              "PHY_RXD3": "+3V3",   # PHYAD0 = 1 -> PHY address 1
              "PHY_RXC": "GND", "PHY_RXCTL": "GND",  # PHYAD1/2 = 0
              "PHY_CFG_EXT": "GND", "PHY_CFG_LDO0": "GND", "PHY_CFG_LDO1": "GND"}  # RGMII I/O at 3.3 V
    for net, rail in straps.items():
        et.add(R(ref("R"), "4.7k", net, rail))
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    decouple(fm, ref, "VADJ", ["10u:0603", "100n"])
    fm.note("LVDS pairs: 100 ohm differential, all 9 pairs of each AD9361 matched to +/- 1 mm.")
    alloc_txt = ", ".join(f"{k}->B{v[0]}.L{v[1]}" for k, v in alloc.items() if isinstance(k, str) and "DCLK" in k)
    fm.note("Clock-capable pins: " + alloc_txt + ", FPGA_REFCLK->B35.L11 (SRCC).")

    # ================================================================ Zynq symbol (all units)
    zs = d.sheet("zynq", "Zynq XC7Z020-1CLG400C (all units)")
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
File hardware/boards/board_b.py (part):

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        elif sig == "3P3V":
            conn[pin] = "+3V3"
        elif sig == "VADJ":
            conn[pin] = "VADJ"
        elif sig == "PG_C2M":
            conn[pin] = "PG_C2M"
        elif sig == "PRSNT_M2C_L":
            conn[pin] = "GND"
        elif sig == "TDI":
            conn[pin] = "FMC_TDI_TDO"  # no JTAG devices on the mezzanine: loop TDI -> TDO
        elif sig == "TDO":
            conn[pin] = "FMC_TDI_TDO"
        elif sig == "CLK0_M2C_P":
            conn[pin] = "FPGA_REFCLK"
    for name, n_la in LVDS_PLAN.items():
        conn[la(n_la, "P")] = f"{name}_P"
        conn[la(n_la, "N")] = f"{name}_N"
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    fm.add(Part("J1", "prc:ASP-134604-01", "FMC LPC (mezzanine)", None, conn, lcsc="C2830435"))
    fm.add(R(ref("R"), "33", "CAL_EN_FPGA", "CAL_EN"))
    fm.add(Part(ref("J"), "Connector_Generic:Conn_01x02", "CAL_EN to board A",
                "Connector_PinHeader_2.54mm:PinHeader_1x02_P2.54mm_Vertical", {"1": "CAL_EN", "2": "GND"}))
    fm.add(R(ref("R"), "100k", "CAL_EN", "GND"))
    fm.note("VADJ must be set to 2.5 V by the carrier (LVDS_25 banks). LA pair plan: tools/fmc.py.")

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

def _alias_lvds(d):
    """AD9361 pins use AD1_DCLK_P etc.; FMC uses the same names -> already identical."""
    return d


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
